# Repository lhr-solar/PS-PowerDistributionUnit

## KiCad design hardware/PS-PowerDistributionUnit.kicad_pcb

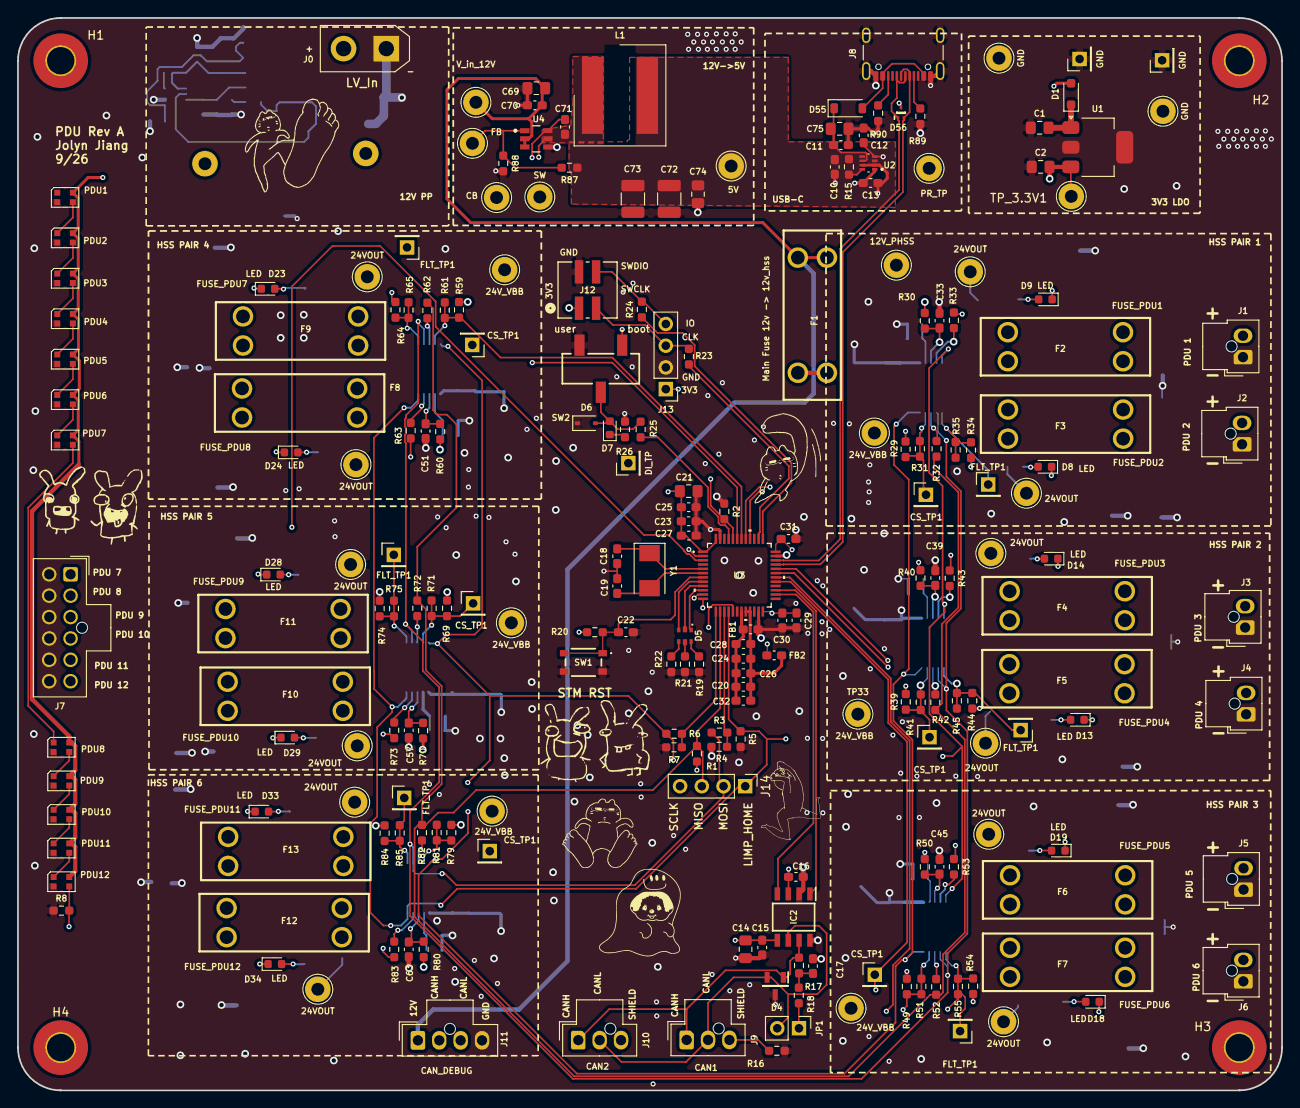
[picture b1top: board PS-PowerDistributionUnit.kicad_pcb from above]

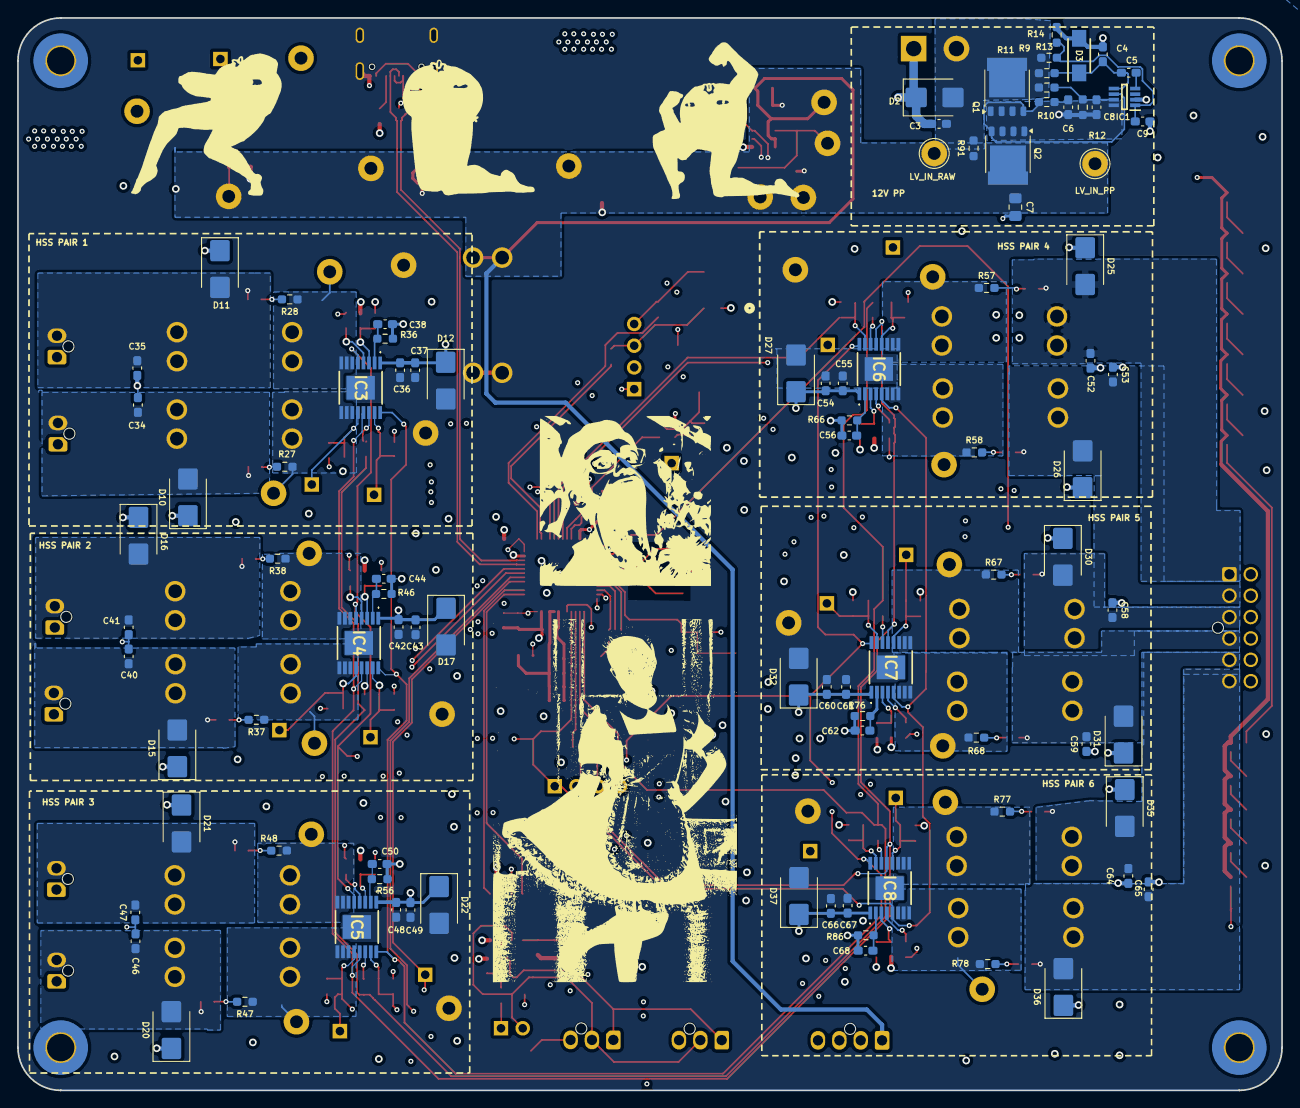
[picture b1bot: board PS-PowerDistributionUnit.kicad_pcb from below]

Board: 4 copper layers, 147.8 x 125.4 mm, 315 parts (93 on the bottom side), 142 nets.

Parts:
C1, C2, C7, C14: 10u; C_0805_2012Metric_Pad1.18x1.45mm_HandSolder
C3, C8, C9, C15, C16, C17: 0.1u; C_0603_1608Metric_Pad1.08x0.95mm_HandSolder
C4, C37, C43, C49, C55, C61, C67: 1u; C_0603_1608Metric_Pad1.08x0.95mm_HandSolder
C5: 220n; C_0603_1608Metric_Pad1.08x0.95mm_HandSolder
C6: 10n; C_0603_1608Metric_Pad1.08x0.95mm_HandSolder
C10, C11, C12, C13, C20, C22, C23, C24, C25, C27, C29, C30, C31: 0.1uF; C_0603_1608Metric_Pad1.08x0.95mm_HandSolder
C18, C19: 26p; C_0603_1608Metric_Pad1.08x0.95mm_HandSolder
C21, C75: 10uF; C_0805_2012Metric_Pad1.18x1.45mm_HandSolder
C26, C28: 1uF; C_0603_1608Metric_Pad1.08x0.95mm_HandSolder
C32: 100nF; C_0603_1608Metric_Pad1.08x0.95mm_HandSolder
C33, C39, C45, C51, C57, C63: 470n; C_0603_1608Metric_Pad1.08x0.95mm_HandSolder
C34, C35, C40, C41, C46, C47, C52, C53, C58, C59, C64, C65, C70, C71: 100n; C_0603_1608Metric_Pad1.08x0.95mm_HandSolder
C36, C42, C48, C54, C60, C66: 1n; C_0603_1608Metric_Pad1.08x0.95mm_HandSolder
C38, C44, C50, C56, C62, C68: 2.2n; C_0603_1608Metric_Pad1.08x0.95mm_HandSolder
C69: 4.7u; C_0805_2012Metric_Pad1.18x1.45mm_HandSolder
C72, C73: 22u; C_1210_3225Metric_Pad1.33x2.70mm_HandSolder
C74: 3.3u; C_0805_2012Metric_Pad1.18x1.45mm_HandSolder
D1: SBA130CH-AU_R1_000A1; D_SOD-323_HandSoldering
D2: SMBJ15CA; D_SMB
D3: SMAF4758A; SODFL5026X125N
D4: CDSOT23-T24CAN
D5: RGB_LED
D6: TVS; D_SOD-323
D7, D8, D9, D13, D14, D18, D19, D23, D24, D28, D29, D33, D34: LED; LED_0603_1608Metric
D10, D11, D12, D15, D16, D17, D20, D21, D22, D25, D26, D27, D30, D31, D32, D35, D36, D37: D_TVS; D_SMB
D38, D39, D40, D41, D42, D43, D44, D45, D46, D47, D48, D49: WS2812B-2020; LED_WS2812B-2020_PLCC4_2.0x2.0mm
D55: D_Schottky; D_SOD-123
D56: TPD2EUSB30DRTR
F1, F2, F3, F4, F5, F6, F7, F8, F9, F10, F11, F12, F13: 5A; Fuse-3557-2
FB1, FB2: FerriteBead; C_0603_1608Metric_Pad1.08x0.95mm_HandSolder
H1, H2, H3, H4: MountingHole_Pad; MountingHole_3.2mm_M3_Pad_TopBottom
IC1: LM74502DDFR
IC2: TCAN3413DR
IC3, IC4, IC5, IC6, IC7, IC8: TPS2HCS08AQPWPRQ1
J0: LV_IN; AMASS_XT30UPB-M_1x02_P5.0mm_Vertical
J1, J2, J3, J4, J5, J6: Conn_01x02; Molex_Nano-Fit_105309-xx02_1x02_P2.50mm_Vertical
J7: LV_0UT2; Molex_Nano-Fit_105310-xx12_2x06_P2.50mm_Vertical
J8: USB_C_Receptacle_USB2.0_16P; USB_C_Receptacle_GCT_USB4105-xx-A_16P_TopMnt_Horizontal
J9: CAN1; Molex_Nano-Fit_105309-xx03_1x03_P2.50mm_Vertical
J10: CAN2; Molex_Nano-Fit_105309-xx03_1x03_P2.50mm_Vertical
J11: CAN_DEBUG; Molex_Nano-Fit_105309-xx04_1x04_P2.50mm_Vertical
J12: SWD_Header; SWD_Conn
J13: SWD; PinHeader_1x04_P2.54mm_Vertical
J14: Conn_01x04; PinHeader_1x04_P2.54mm_Vertical
JP1: TRM; PinHeader_1x02_P2.54mm_Vertical
L1: 8.2u; 74439369082
Q1, Q2: PSMN012-100YS; LFPAK56
R1, R2, R4, R5, R7, R8, R9, R15, R20, R25, R29, R33, R35, R39, R43, R45, R49, R53, R55, R59, R63, R65, R69, R73, R75, R79, R83, R85: 10k; R_0603_1608Metric_Pad0.98x0.95mm_HandSolder
R3, R6, R23, R24, R31, R32, R41, R42, R51, R52, R61, R62, R71, R72, R81, R82: 22; R_0603_1608Metric_Pad0.98x0.95mm_HandSolder
R10: 33; R_0603_1608Metric_Pad0.98x0.95mm_HandSolder
R11, R13, R87: 100k; R_0603_1608Metric_Pad0.98x0.95mm_HandSolder
R12: 7.32k; R_0603_1608Metric_Pad0.98x0.95mm_HandSolder
R14: 15.8k; R_0603_1608Metric_Pad0.98x0.95mm_HandSolder
R16, R91: 0; R_0603_1608Metric_Pad0.98x0.95mm_HandSolder
R17, R18: 60; R_0603_1608Metric_Pad0.98x0.95mm_HandSolder
R19, R21, R22, R26, R36, R46, R56, R66, R76, R86: 1k; R_0603_1608Metric_Pad0.98x0.95mm_HandSolder
R27, R28, R34, R37, R38, R44, R47, R48, R54, R57, R58, R64, R67, R68, R74, R77, R78, R84: 4.7k; R_0603_1608Metric_Pad0.98x0.95mm_HandSolder
R30, R40, R50, R60, R70, R80: 10; R_0603_1608Metric_Pad0.98x0.95mm_HandSolder
R88: 19.1k; R_0603_1608Metric_Pad0.98x0.95mm_HandSolder
R89, R90: 5.1k; R_0603_1608Metric_Pad0.98x0.95mm_HandSolder
SW1: Reset; TL3365AF180QG
SW2: SW_SPDT; BootSW
TP4: DI_TP; PinHeader_1x01_P2.54mm_Vertical
TP6, TP7, TP8, TP9, TP10, TP11: FLT_TP1; PinHeader_1x01_P2.54mm_Vertical
TP12, TP13, TP14, TP15, TP16, TP17: CS_TP1; PinHeader_1x01_P2.54mm_Vertical
TP18: 12V_PHSS; TestPoint_THTPad_D3.0mm_Drill1.5mm
TP19, TP20: GND; TestPoint_THTPad_D3.0mm_Drill1.5mm
TP21, TP22: GND; PinHeader_1x01_P2.54mm_Vertical
TP23: LV_IN_RAW; TestPoint_THTPad_D3.0mm_Drill1.5mm
TP24: LV_IN_PP; TestPoint_THTPad_D3.0mm_Drill1.5mm
TP27: PR_TP; TestPoint_THTPad_D3.0mm_Drill1.5mm
TP28: 5V; TestPoint_THTPad_D3.0mm_Drill1.5mm
TP30, TP33, TP36, TP39, TP42, TP45: 24V_VBB; TestPoint_THTPad_D3.0mm_Drill1.5mm
TP31, TP32, TP34, TP35, TP37, TP38, TP40, TP41, TP43, TP44, TP46, TP47: 24VOUT; TestPoint_THTPad_D3.0mm_Drill1.5mm
TP48: V_in_12V; TestPoint_THTPad_D3.0mm_Drill1.5mm
TP49: CB; TestPoint_THTPad_D3.0mm_Drill1.5mm
TP50: FB; TestPoint_THTPad_D3.0mm_Drill1.5mm
TP51: SW; TestPoint_THTPad_D3.0mm_Drill1.5mm
TP_3.3V1: 3.3V; TestPoint_THTPad_D3.0mm_Drill1.5mm
U1: MCP1826S; SOT-223-3_TabPin2
U2: TPS2117DRLR
U3: STM32G473CETx; 48PinMCU
U4: LMR51635XDDCR; DDC0006A-MFG
Y1: Crystal; Crystal_SMD_Abracon_ABM3-2Pin_5.0x3.2mm

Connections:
+3V3: C2.2, C14.1, C15.1, C16.1, C21.1, C23.1, C25.1, C27.1, C29.1, C30.1, C31.1, FB2.1, IC2.3 (VCC), IC2.5 (SHDNV_IO), J12.1, J13.1, R1.2, R20.2, R29.1, R30.1, R34.1, R39.1, R40.1, R44.1, R49.1, R50.1, R54.1, R59.1, R60.1, R64.1, R69.1, R70.1, R74.1, R79.1, R80.1, R84.1, SW2.1 (A), TP_3.3V1.1 (1_1), U1.3 (VO), U3.1 (VBAT), U3.24 (VDD), U3.36 (VDD), U3.48 (VDD)
+5V: C13.1, D1.2 (A), D38.4 (VDD), D39.4 (VDD), D40.4 (VDD), D41.4 (VDD), D42.4 (VDD), D43.4 (VDD), D44.4 (VDD), D45.4 (VDD), D46.4 (VDD), D47.4 (VDD), D48.4 (VDD), D49.4 (VDD), U2.2 (VOUT), U2.7 (VOUT__1)
+12V: C7.1, C69.1, C70.1, F1.2, J11.1 (12V), Q2.5, R91.2, TP24.1 (1_1), TP48.1 (1_1), U4.2 (EN), U4.3 (VIN)
/48PinMCU/BOOT0: R25.1, U3.45 (PB8-BOOT0)
/48PinMCU/GNDA: C20.2, C24.2, C26.2, C28.2, C32.2, FB1.1, U3.19 (VSSA)
/48PinMCU/NRST: C22.1, R20.1, SW1.1, U3.7 (PG10-NRST)
/48PinMCU/PA0: D5.5, U3.8 (PA0-GPIO_BLUE)
/48PinMCU/PA1: D5.3, U3.9 (PA1_GPIO_RED)
/48PinMCU/PA2: D5.1, U3.10 (PA2-GPIO_GREEN)
/48PinMCU/PA5: R6.2, R7.2, U3.13 (PA5)
/48PinMCU/PA7: R3.2, R4.2, U3.15 (PA7)
/48PinMCU/PB1: D38.3 (DIN), R8.2, U3.17 (PB1)
/48PinMCU/PB12: IC2.4 (RXD), U3.26 (PB12)
/48PinMCU/PB13: IC2.1 (TXD), U3.27 (PB13)
/48PinMCU/SWCLK: R23.1, U3.38 (PA14)
/48PinMCU/SWDIO: R24.1, U3.37 (PA13)
/48PinMCU/VDDA: C20.1, C24.1, C26.1, C28.1, C32.1, FB2.2, U3.20 (VREF+), U3.21 (VDDA)
/+12V_HSS: C36.1, C37.1, C42.1, C43.1, C48.1, C49.1, C54.1, C55.1, C60.1, C61.1, C66.1, C67.1, D12.2 (A2), D17.2 (A2), D22.2 (A2), D27.2 (A2), D32.2 (A2), D37.2 (A2), F1.1, IC3.17 (VBB), IC4.17 (VBB), IC5.17 (VBB), IC6.17 (VBB), IC7.17 (VBB), IC8.17 (VBB), TP18.1 (1_1), TP30.1 (1_1), TP33.1 (1_1), TP36.1 (1_1), TP39.1 (1_1), TP42.1 (1_1), TP45.1 (1_1)
/CAN/CAN_H: D4.1 (CAN_H), IC2.7 (CANH), J9.1 (CAN_H), J10.1 (CAN_H), J11.2 (CAN_H), R17.1
/CAN/CAN_L: D4.2 (CAN_L), IC2.6 (CANL), J9.2 (CAN_L), J10.2 (CAN_L), J11.3 (CAN_L), JP1.2 (B)
/CAN/SHIELD: J9.3 (SHIELD), J10.3 (SHIELD), R16.1
/DI_MODE: R2.2, R33.1, R43.1, R53.1, R63.1, R73.1, R83.1, TP4.1 (1_1), U3.44 (PB7)
/LIMP_HOME: IC3.5 (LHI), IC4.5 (LHI), IC5.5 (LHI), IC6.5 (LHI), IC7.5 (LHI), IC8.5 (LHI), J14.1, R5.2, U3.16 (PB0)
/MISO: J14.3, R1.1, R32.1, R42.1, R52.1, R62.1, R72.1, R82.1, U3.14 (PA6)
/MOSI: IC3.13 (SDI), IC4.13 (SDI), IC5.13 (SDI), IC6.13 (SDI), IC7.13 (SDI), IC8.13 (SDI), J14.2, R3.1
/OUTPUT1: C35.2, D9.1 (K), D11.2 (A2), F2.2, J1.2
/OUTPUT2: C34.2, D8.1 (K), D10.2 (A2), F3.2, J2.2
/OUTPUT3: C41.2, D14.1 (K), D16.2 (A2), F4.2, J3.2
/OUTPUT4: C40.2, D13.1 (K), D15.2 (A2), F5.2, J4.2
/OUTPUT5: C47.2, D19.1 (K), D21.2 (A2), F6.2, J5.2
/OUTPUT6: C46.2, D18.1 (K), D20.2 (A2), F7.2, J6.2
/OUTPUT7: C52.2, D23.1 (K), D25.2 (A2), F9.2, J7.1
/OUTPUT8: C53.2, D24.1 (K), D26.2 (A2), F8.2, J7.2
/OUTPUT9: C58.2, D28.1 (K), D30.2 (A2), F11.2, J7.3
/OUTPUT10: C59.2, D29.1 (K), D31.2 (A2), F10.2, J7.4
/OUTPUT11: C64.2, D33.1 (K), D35.2 (A2), F13.2, J7.5
/OUTPUT12: C65.2, D34.1 (K), D36.2 (A2), F12.2, J7.6
/Pair1/FLT_WAKE: IC3.12 (~FLT_/_~WAKE_SIG), R34.2, R35.1, R35.2, TP6.1 (1_1), U3.41 (PB4)
/Pair1/SPI_CS: IC3.15 (NCS), R29.2, R31.1, R31.2, TP12.1 (1_1), U3.40 (PB3)
/Pair1/VDD: C33.1, IC3.3 (VDD), R30.2
/Pair1/VOUT1: F2.1, IC3.6 (VOUT1_1), IC3.7 (VOUT1_2), IC3.8 (VOUT1_3), R28.1, TP31.1 (1_1)
/Pair1/VOUT2: F3.1, IC3.9 (VOUT2_1), IC3.10 (VOUT2_2), IC3.11 (VOUT2_3), R27.1, TP32.1 (1_1)
/Pair2/FLT_WAKE: IC4.12 (~FLT_/_~WAKE_SIG), R44.2, R45.1, R45.2, TP7.1 (1_1), U3.32 (PA10)
/Pair2/SPI_CS: IC4.15 (NCS), R39.2, R41.1, R41.2, TP13.1 (1_1), U3.31 (PA9)
/Pair2/VDD: C39.1, IC4.3 (VDD), R40.2
/Pair2/VOUT1: F4.1, IC4.6 (VOUT1_1), IC4.7 (VOUT1_2), IC4.8 (VOUT1_3), R38.1, TP34.1 (1_1)
/Pair2/VOUT2: F5.1, IC4.9 (VOUT2_1), IC4.10 (VOUT2_2), IC4.11 (VOUT2_3), R37.1, TP35.1 (1_1)
/Pair3/FLT_WAKE: IC5.12 (~FLT_/_~WAKE_SIG), R54.2, R55.1, R55.2, TP8.1 (1_1), U3.30 (PA8)
/Pair3/SPI_CS: IC5.15 (NCS), R49.2, R51.1, R51.2, TP14.1 (1_1), U3.29 (PB15)
/Pair3/VDD: C45.1, IC5.3 (VDD), R50.2
/Pair3/VOUT1: F6.1, IC5.6 (VOUT1_1), IC5.7 (VOUT1_2), IC5.8 (VOUT1_3), R48.1, TP37.1 (1_1)
/Pair3/VOUT2: F7.1, IC5.9 (VOUT2_1), IC5.10 (VOUT2_2), IC5.11 (VOUT2_3), R47.1, TP38.1 (1_1)
/Pair4/FLT_WAKE: IC6.12 (~FLT_/_~WAKE_SIG), R64.2, R65.1, R65.2, TP9.1 (1_1), U3.43 (PB6)
/Pair4/SPI_CS: IC6.15 (NCS), R59.2, R61.1, R61.2, TP15.1 (1_1), U3.42 (PB5)
/Pair4/VDD: C51.1, IC6.3 (VDD), R60.2
/Pair4/VOUT1: F8.1, IC6.6 (VOUT1_1), IC6.7 (VOUT1_2), IC6.8 (VOUT1_3), R58.1, TP40.1 (1_1)
/Pair4/VOUT2: F9.1, IC6.9 (VOUT2_1), IC6.10 (VOUT2_2), IC6.11 (VOUT2_3), R57.1, TP41.1 (1_1)
/Pair5/FLT_WAKE: IC7.12 (~FLT_/_~WAKE_SIG), R74.2, R75.1, R75.2, TP10.1 (1_1), U3.3 (PC14-OSC32_IN)
/Pair5/SPI_CS: IC7.15 (NCS), R69.2, R71.1, R71.2, TP16.1 (1_1), U3.2 (PC13)
/Pair5/VDD: C57.1, IC7.3 (VDD), R70.2
/Pair5/VOUT1: F10.1, IC7.6 (VOUT1_1), IC7.7 (VOUT1_2), IC7.8 (VOUT1_3), R68.1, TP43.1 (1_1)
/Pair5/VOUT2: F11.1, IC7.9 (VOUT2_1), IC7.10 (VOUT2_2), IC7.11 (VOUT2_3), R67.1, TP44.1 (1_1)
/Pair6/FLT_WAKE: IC8.12 (~FLT_/_~WAKE_SIG), R84.2, R85.1, R85.2, TP11.1 (1_1), U3.11 (PA3)
/Pair6/SPI_CS: IC8.15 (NCS), R79.2, R81.1, R81.2, TP17.1 (1_1), U3.12 (PA4)
/Pair6/VDD: C63.1, IC8.3 (VDD), R80.2
/Pair6/VOUT1: F12.1, IC8.6 (VOUT1_1), IC8.7 (VOUT1_2), IC8.8 (VOUT1_3), R78.1, TP46.1 (1_1)
/Pair6/VOUT2: F13.1, IC8.9 (VOUT2_1), IC8.10 (VOUT2_2), IC8.11 (VOUT2_3), R77.1, TP47.1 (1_1)
/Power_usb/12VBuck/CB: C71.1, TP49.1 (1_1), U4.6 (CB)
/Power_usb/12VBuck/FB: R87.2, R88.1, TP50.1 (1_1), U4.1 (FB)
/Power_usb/12VBuck/SW: C71.2, L1.1, TP51.1 (1_1), U4.5 (SW)
/Power_usb/12V_INPUT: C3.1, D2.2 (A2), J0.2, Q1.5, R9.2, R11.1, R13.1, R91.1, TP23.1 (1_1)
/Power_usb/Buck_5V: C10.1, C72.1, C73.1, C74.1, L1.2, R15.1, R87.1, TP28.1 (1_1), U2.3 (VIN1), U2.5 (MODE)
/Power_usb/D+: D56.2 (D-), J8.A7 (D-), J8.B7 (D-), U3.33 (PA11)
/Power_usb/D-: D56.1 (D+), J8.A6 (D+), J8.B6 (D+), U3.34 (PA12)
/Power_usb/PowerProtection/EN/UVLO: C9.2, IC1.1 (EN/UVLO), R13.2, R14.2
/Power_usb/PowerProtection/OV: C8.2, IC1.7 (OV), R11.2, R12.1
/Power_usb/PowerProtection/gate: IC1.6 (GATE), Q1.4, Q2.4, R10.2
/Power_usb/PowerProtection/source: IC1.8 (SRC), Q1.1, Q1.2, Q1.3, Q2.1, Q2.2, Q2.3
/Power_usb/Power_Mux/PR1: C12.1, TP27.1 (1_1), U2.4 (PR1)
/Power_usb/Power_Mux/VIN_2: C11.1, C75.2, D55.1 (K), U2.6 (VIN2)
/Power_usb/USB-C Connector/CC1: J8.A5 (CC1), R89.2
/Power_usb/USB-C Connector/CC2: J8.B5 (CC2), R90.2
/Power_usb/USB-C Connector/VBUS_IN: D55.2 (A), J8.A4 (VBUS), J8.A9 (VBUS), J8.B4 (VBUS), J8.B9 (VBUS)
/SCLK: IC3.16 (SCLK), IC4.16 (SCLK), IC5.16 (SCLK), IC6.16 (SCLK), IC7.16 (SCLK), IC8.16 (SCLK), J14.4, R6.1
GND: C1.1, C2.1, C3.2, C4.1, C6.2, C7.2, C8.1, C9.1, C10.2, C11.2, C12.2, C13.2, C14.2, C15.2, C16.2, C17.1, C18.1, C19.2, C21.2, C22.2, C23.2, C25.2, C27.2, C29.2, C30.2, C31.2, C33.2, C34.1, C35.1, C36.2, C37.2, C38.2, C39.2, C40.1, C41.1, C42.2, C43.2, C44.2, C45.2, C46.1, C47.1, C48.2, C49.2, C50.2, C51.2, C52.1, C53.1, C54.2, C55.2, C56.2, C57.2, C58.1, C59.1, C60.2, C61.2, C62.2, C63.2, C64.1, C65.1, C66.2, C67.2, C68.2, C69.2, C70.2, C72.2, C73.2, C74.2, C75.1, D2.1 (A1), D3.2 (A), D4.3 (GND), D6.1 (A1), D10.1 (A1), D11.1 (A1), D12.1 (A1), D15.1 (A1), D16.1 (A1), D17.1 (A1), D20.1 (A1), D21.1 (A1), D22.1 (A1), D25.1 (A1), D26.1 (A1), D27.1 (A1), D30.1 (A1), D31.1 (A1), D32.1 (A1), D35.1 (A1), D36.1 (A1), D37.1 (A1), D38.2 (VSS), D39.2 (VSS), D40.2 (VSS), D41.2 (VSS), D42.2 (VSS), D43.2 (VSS), D44.2 (VSS), D45.2 (VSS), D46.2 (VSS), D47.2 (VSS), D48.2 (VSS), D49.2 (VSS), D56.3 (GND), FB1.2, IC1.2 (GND), IC2.2 (GND), IC2.8 (STB), IC3.1 (GND), IC4.1 (GND), IC5.1 (GND), IC6.1 (GND), IC7.1 (GND), IC8.1 (GND), J0.1, J1.1, J2.1, J3.1, J4.1, J5.1, J6.1, J7.7, J7.8, J7.9, J7.10, J7.11, J7.12, J8.A1 (GND), J8.A12 (GND), J8.B1 (GND), J8.B12 (GND), J8.S1 (SHIELD), J8.S2 (Shield), J8.S3 (Shield), J8.S4 (Shield), J11.4 (GND), J12.2, J13.2, R2.1, R4.1, R5.1, R7.1, R8.1, R12.2, R14.1, R16.2, R19.2, R21.2, R22.2, R26.2, R36.1, R46.1, R56.1, R66.1, R76.1, R86.1, R88.2, R89.1, R90.1, SW1.2, SW2.3 (C), TP19.1 (1_1), TP20.1 (1_1), TP21.1 (1_1), TP22.1 (1_1), U1.2 (GND), U2.1 (GND), U3.23 (VSS), U3.35 (VSS), U3.47 (VSS), U4.4 (GND)
unnamed: C6.1, R10.1
unnamed: C17.2, R17.2, R18.1
unnamed: C1.2, D1.1 (K), U1.1 (VI)
unnamed: C4.2, C5.1, D3.1 (K), IC1.5 (VS), R9.1
unnamed: D5.2, R19.1
unnamed: D5.4, R21.1
unnamed: D5.6, R22.1
unnamed: D6.2 (A2), D7.2 (A), R25.2, SW2.2 (B)
unnamed: D7.1 (K), R26.1
unnamed: D8.2 (A), R27.2
unnamed: D9.2 (A), R28.2
unnamed: D13.2 (A), R37.2
unnamed: D14.2 (A), R38.2
unnamed: D18.2 (A), R47.2
unnamed: D19.2 (A), R48.2
unnamed: D23.2 (A), R57.2
unnamed: D24.2 (A), R58.2
unnamed: D28.2 (A), R67.2
unnamed: D29.2 (A), R68.2
unnamed: D33.2 (A), R77.2
unnamed: D34.2 (A), R78.2
unnamed: D38.1 (DOUT), D39.3 (DIN)
unnamed: D39.1 (DOUT), D40.3 (DIN)
unnamed: D40.1 (DOUT), D41.3 (DIN)
unnamed: D41.1 (DOUT), D42.3 (DIN)
unnamed: D42.1 (DOUT), D44.3 (DIN)
unnamed: D43.3 (DIN), D45.1 (DOUT)
unnamed: D44.1 (DOUT), D46.3 (DIN)
unnamed: D45.3 (DIN), D47.1 (DOUT)
unnamed: D46.1 (DOUT), D48.3 (DIN)
unnamed: D47.3 (DIN), D49.1 (DOUT)
unnamed: D48.1 (DOUT), D49.3 (DIN)
unnamed: C5.2, IC1.4 (VCAP)
unnamed: IC3.4 (DI), R33.2
unnamed: IC3.14 (SDO), R32.2
unnamed: C38.1, IC3.2 (SNS), R36.2
unnamed: IC4.4 (DI), R43.2
unnamed: IC4.14 (SDO), R42.2
unnamed: C44.1, IC4.2 (SNS), R46.2
unnamed: IC5.4 (DI), R53.2
unnamed: IC5.14 (SDO), R52.2
unnamed: C50.1, IC5.2 (SNS), R56.2
unnamed: IC6.4 (DI), R63.2
unnamed: IC6.14 (SDO), R62.2
unnamed: C56.1, IC6.2 (SNS), R66.2
unnamed: IC7.4 (DI), R73.2
unnamed: IC7.14 (SDO), R72.2
unnamed: C62.1, IC7.2 (SNS), R76.2
unnamed: IC8.4 (DI), R83.2
unnamed: IC8.14 (SDO), R82.2
unnamed: C68.1, IC8.2 (SNS), R86.2
unnamed: J12.3, J13.3, R23.2
unnamed: J12.4, J13.4, R24.2
unnamed: JP1.1 (A), R18.2
unnamed: R15.2, U2.8 (ST)
unnamed: C18.2, U3.5 (PF0-OSC_IN), Y1.1
unnamed: C19.1, U3.6 (PF1-OSC_OUT), Y1.2

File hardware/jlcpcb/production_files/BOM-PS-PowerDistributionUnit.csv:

Comment,Designator,Footprint,LCSC,Quantity
0.1u,"C15,C16,C17,C3,C8,C9",C_0603_1608Metric_Pad1.08x0.95mm_HandSolder,C1591,6
0.1uF,"C10,C11,C12,C13,C20,C22,C23,C24,C25,C27,C29,C30,C31",C_0603_1608Metric_Pad1.08x0.95mm_HandSolder,C1591,13
10,"R30,R40,R50,R60,R70,R80",R_0603_1608Metric_Pad0.98x0.95mm_HandSolder,C313648,6
100k,"R11,R13,R87",R_0603_1608Metric_Pad0.98x0.95mm_HandSolder,C25803,3
100n,"C34,C35,C40,C41,C46,C47,C52,C53,C58,C59,C64,C65,C70,C71",C_0603_1608Metric_Pad1.08x0.95mm_HandSolder,C1591,14
100nF,C32,C_0603_1608Metric_Pad1.08x0.95mm_HandSolder,C1591,1
10k,"R1,R15,R2,R20,R25,R29,R33,R35,R39,R4,R43,R45,R49,R5,R53,R55,R59,R63,R65,R69,R7,R73,R75,R79,R8,R83,R85,R9",R_0603_1608Metric_Pad0.98x0.95mm_HandSolder,C25804,28
10n,C6,C_0603_1608Metric_Pad1.08x0.95mm_HandSolder,C57112,1
10u,"C1,C14,C2,C7",C_0805_2012Metric_Pad1.18x1.45mm_HandSolder,C440198,4
10uF,"C21,C75",C_0805_2012Metric_Pad1.18x1.45mm_HandSolder,C440198,2
15.8k,R14,R_0603_1608Metric_Pad0.98x0.95mm_HandSolder,C2090646,1
19.1k,R88,R_0603_1608Metric_Pad0.98x0.95mm_HandSolder,C844132,1
1k,"R19,R21,R22,R26,R36,R46,R56,R66,R76,R86",R_0603_1608Metric_Pad0.98x0.95mm_HandSolder,C21190,10
1n,"C36,C42,C48,C54,C60,C66",C_0603_1608Metric_Pad1.08x0.95mm_HandSolder,C100040,6
1u,"C37,C4,C43,C49,C55,C61,C67",C_0603_1608Metric_Pad1.08x0.95mm_HandSolder,C15849,7
1uF,"C26,C28",C_0603_1608Metric_Pad1.08x0.95mm_HandSolder,C15849,2
2.2n,"C38,C44,C50,C56,C62,C68",C_0603_1608Metric_Pad1.08x0.95mm_HandSolder,C5254613,6
22,"R23,R24,R3,R31,R32,R41,R42,R51,R52,R6,R61,R62,R71,R72,R81,R82",R_0603_1608Metric_Pad0.98x0.95mm_HandSolder,C107701,16
220n,C5,C_0603_1608Metric_Pad1.08x0.95mm_HandSolder,C344195,1
22u,"C72,C73",C_1210_3225Metric_Pad1.33x2.70mm_HandSolder,C5448976,2
26p,"C18,C19",C_0603_1608Metric_Pad1.08x0.95mm_HandSolder,C92670,2
3.3u,C74,C_0805_2012Metric_Pad1.18x1.45mm_HandSolder,C342775,1
33,R10,R_0603_1608Metric_Pad0.98x0.95mm_HandSolder,C844927,1
4.7k,"R27,R28,R34,R37,R38,R44,R47,R48,R54,R57,R58,R64,R67,R68,R74,R77,R78,R84",R_0603_1608Metric_Pad0.98x0.95mm_HandSolder,C23162,18
4.7u,C69,C_0805_2012Metric_Pad1.18x1.45mm_HandSolder,C105911,1
470n,"C33,C39,C45,C51,C57,C63",C_0603_1608Metric_Pad1.08x0.95mm_HandSolder,C106851,6
5.1k,"R89,R90",R_0603_1608Metric_Pad0.98x0.95mm_HandSolder,C23186,2
5A,"F1,F10,F11,F12,F13,F2,F3,F4,F5,F6,F7,F8,F9",Fuse-3557-2,C3205238,13
60,"R17,R18",R_0603_1608Metric_Pad0.98x0.95mm_HandSolder,C166918,2
7.32k,R12,R_0603_1608Metric_Pad0.98x0.95mm_HandSolder,C25804,1
8.2u,L1,74439369082,C1870586,1
CAN1,J9,Molex_Nano-Fit_105309-xx03_1x03_P2.50mm_Vertical,C17504794,1
CAN2,J10,Molex_Nano-Fit_105309-xx03_1x03_P2.50mm_Vertical,C17504794,1
CAN_DEBUG,J11,Molex_Nano-Fit_105309-xx04_1x04_P2.50mm_Vertical,C586230,1
CDSOT23-T24CAN,D4,CDSOT23-T24CAN,C2959841,1
CS_TP1,"TP12,TP13,TP14,TP15,TP16,TP17",PinHeader_1x01_P2.54mm_Vertical,C41426955,6
Conn_01x02,"J1,J2,J3,J4,J5,J6",Molex_Nano-Fit_105309-xx02_1x02_P2.50mm_Vertical,C2938824,6
Crystal,Y1,Crystal_SMD_Abracon_ABM3-2Pin_5.0x3.2mm,C144380,1
DI_TP,TP4,PinHeader_1x01_P2.54mm_Vertical,C41426955,1
D_Schottky,D55,D_SOD-123,C82544,1
D_TVS,"D10,D11,D12,D15,D16,D17,D20,D21,D22,D25,D26,D27,D30,D31,D32,D35,D36,D37",D_SMB,C428853,18
FLT_TP1,"TP10,TP11,TP6,TP7,TP8,TP9",PinHeader_1x01_P2.54mm_Vertical,C41426955,6
FerriteBead,"FB1,FB2",C_0603_1608Metric_Pad1.08x0.95mm_HandSolder,C354394,2
GND,"TP21,TP22",PinHeader_1x01_P2.54mm_Vertical,C41426955,2
LED,D7,LED_0603_1608Metric,C125103,1
LED,"D13,D14,D18,D19,D23,D24,D28,D29,D33,D34,D8,D9",LED_0603_1608Metric,C84263,12
LM74502DDFR,IC1,LM74502DDFR,C3236215,1
LMR51635XDDCR,U4,DDC0006A-MFG,C42432812,1
LV_0UT2,J7,Molex_Nano-Fit_105310-xx12_2x06_P2.50mm_Vertical,C485572,1
MCP1826S,U1,SOT-223-3_TabPin2,C126055,1
PSMN012-100YS,"Q1,Q2",LFPAK56,C20443035,2
RGB_LED,D5,RGB_LED,C264519,1
Reset,SW1,TL3365AF180QG,C2886926,1
SBA130CH-AU_R1_000A1,D1,D_SOD-323_HandSoldering,C191023,1
SMAF4758A,D3,SODFL5026X125N,C183490,1
SMBJ15CA,D2,D_SMB,C669039,1
STM32G473CETx,U3,48PinMCU,C730113,1
SWD,J13,PinHeader_1x04_P2.54mm_Vertical,C2691448,1
SWD_Header,J12,SWD_Conn,C17492485,1
TCAN3413DR,IC2,TCAN3413DR,C22433320,1
TPD2EUSB30DRTR,D56,TPD2EUSB30DRTR,C97502,1
TPS2117DRLR,U2,TPS2117DRLR,C22399676,1
TRM,JP1,PinHeader_1x02_P2.54mm_Vertical,C492401,1
TVS,D6,D_SOD-323,C725495,1
WS2812B-2020,"D38,D39,D40,D41,D42,D43,D44,D45,D46,D47,D48,D49",LED_WS2812B-2020_PLCC4_2.0x2.0mm,C965555,12
24VOUT,TP37,TestPoint_THTPad_D3.0mm_Drill1.5mm,,1
12V_PHSS,TP18,TestPoint_THTPad_D3.0mm_Drill1.5mm,,1
24V_VBB,TP36,TestPoint_THTPad_D3.0mm_Drill1.5mm,,1
24VOUT,TP35,TestPoint_THTPad_D3.0mm_Drill1.5mm,,1
24VOUT,TP46,TestPoint_THTPad_D3.0mm_Drill1.5mm,,1
GND,TP20,TestPoint_THTPad_D3.0mm_Drill1.5mm,,1
Conn_01x04,J14,PinHeader_1x04_P2.54mm_Vertical,,1
USB_C_Receptacle_USB2.0_16P,J8,USB_C_Receptacle_GCT_USB4105-xx-A_16P_TopMnt_Horizontal,,1
24V_VBB,TP39,TestPoint_THTPad_D3.0mm_Drill1.5mm,,1
24VOUT,TP34,TestPoint_THTPad_D3.0mm_Drill1.5mm,,1
24V_VBB,TP45,TestPoint_THTPad_D3.0mm_Drill1.5mm,,1
24VOUT,TP31,TestPoint_THTPad_D3.0mm_Drill1.5mm,,1
SW_SPDT,SW2,BootSW,,1
LV_IN,J0,AMASS_XT30UPB-M_1x02_P5.0mm_Vertical,,1
24VOUT,TP32,TestPoint_THTPad_D3.0mm_Drill1.5mm,,1
SW,TP51,TestPoint_THTPad_D3.0mm_Drill1.5mm,,1
24V_VBB,TP30,TestPoint_THTPad_D3.0mm_Drill1.5mm,,1
PR_TP,TP27,TestPoint_THTPad_D3.0mm_Drill1.5mm,,1
24VOUT,TP41,TestPoint_THTPad_D3.0mm_Drill1.5mm,,1
24VOUT,TP43,TestPoint_THTPad_D3.0mm_Drill1.5mm,,1
5V,TP28,TestPoint_THTPad_D3.0mm_Drill1.5mm,,1
24V_VBB,TP42,TestPoint_THTPad_D3.0mm_Drill1.5mm,,1
24VOUT,TP44,TestPoint_THTPad_D3.0mm_Drill1.5mm,,1
24VOUT,TP40,TestPoint_THTPad_D3.0mm_Drill1.5mm,,1
V_in_12V,TP48,TestPoint_THTPad_D3.0mm_Drill1.5mm,,1
24V_VBB,TP33,TestPoint_THTPad_D3.0mm_Drill1.5mm,,1
24VOUT,TP47,TestPoint_THTPad_D3.0mm_Drill1.5mm,,1
24VOUT,TP38,TestPoint_THTPad_D3.0mm_Drill1.5mm,,1
GND,TP19,TestPoint_THTPad_D3.0mm_Drill1.5mm,,1
FB,TP50,TestPoint_THTPad_D3.0mm_Drill1.5mm,,1
CB,TP49,TestPoint_THTPad_D3.0mm_Drill1.5mm,,1
TPS2HCS08AQPWPRQ1,IC8,TPS2HCS08AQPWPRQ1,,1
TPS2HCS08AQPWPRQ1,IC4,TPS2HCS08AQPWPRQ1,,1
LV_IN_PP,TP24,TestPoint_THTPad_D3.0mm_Drill1.5mm,,1
TPS2HCS08AQPWPRQ1,IC3,TPS2HCS08AQPWPRQ1,,1
TPS2HCS08AQPWPRQ1,IC6,TPS2HCS08AQPWPRQ1,,1
TPS2HCS08AQPWPRQ1,IC7,TPS2HCS08AQPWPRQ1,,1
TPS2HCS08AQPWPRQ1,IC5,TPS2HCS08AQPWPRQ1,,1

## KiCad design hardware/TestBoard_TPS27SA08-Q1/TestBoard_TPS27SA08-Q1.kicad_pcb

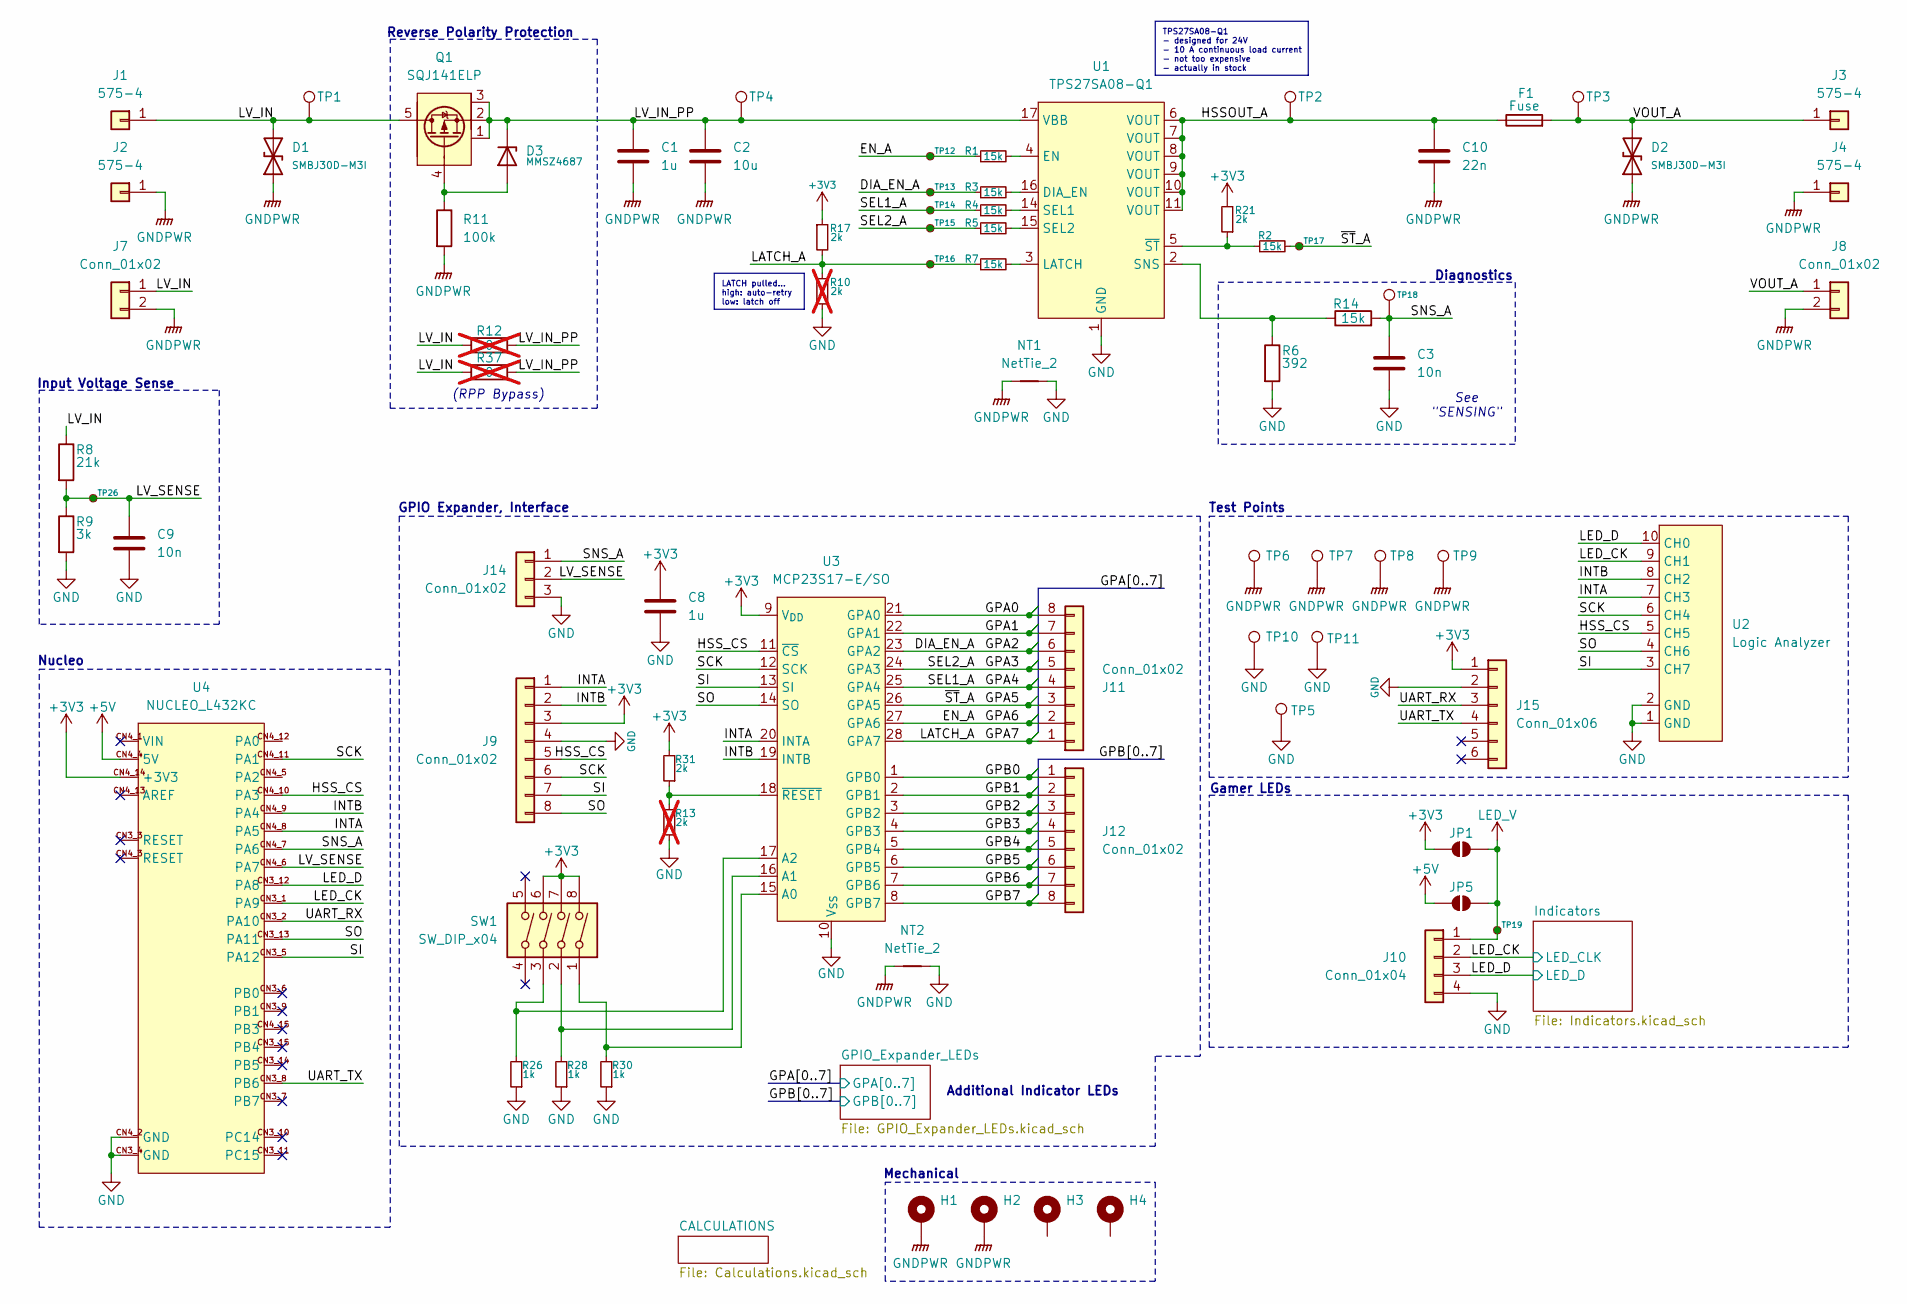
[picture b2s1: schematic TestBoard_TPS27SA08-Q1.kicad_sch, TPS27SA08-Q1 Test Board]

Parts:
C1, C8: 1u; C_0805_2012Metric
C2: 10u; C_0805_2012Metric
C3, C9: 10n; C_0805_2012Metric
C10: 22n; C_0805_2012Metric
D1, D2: SMBJ30D-M3I; D_SMB
D3: MMSZ4687; D_SOD-123
F1: Fuse; Fuseholder_Blade_Mini_Keystone_3568
H1, H2, H3, H4: MountingHole_Pad; MountingHole_3.2mm_M3_Pad
J1, J2, J3, J4: 575-4; 5754
J7, J8: Conn_01x02; TerminalBlock_MaiXu_MX126-5.0-02P_1x02_P5.00mm
J9, J11, J12: Conn_01x02; PinHeader_1x08_P2.54mm_Vertical
J10: Conn_01x04; PinHeader_1x04_P2.54mm_Vertical
J14: Conn_01x02; PinHeader_1x03_P2.54mm_Vertical
J15: Conn_01x06; PinSocket_1x06_P2.54mm_Vertical
JP1, JP5: SolderJumper_2_Open; SolderJumper-2_P1.3mm_Open_RoundedPad1.0x1.5mm
NT1, NT2: NetTie_2; NetTie-2_SMD_Pad0.5mm
Q1: SQJ141ELP; PowerPAK_SO-8L_Single
R1, R2, R3, R4, R5, R7, R14: 15k; R_0805_2012Metric
R6: 392; R_0805_2012Metric
R8: 21k; R_0805_2012Metric
R9: 3k; R_0805_2012Metric
R10, R13: 2k; R_0805_2012Metric; not fitted
R11: 100k; R_0805_2012Metric
R12, R37: 0; R_0805_2012Metric; not fitted
R17, R21, R31: 2k; R_0805_2012Metric
R26, R28, R30: 1k; R_0805_2012Metric
SW1: SW_DIP_x04; ADE04S04
TP1, TP2, TP3, TP4, TP5, TP6, TP7, TP8, TP9, TP10, TP11: TestPoint; PinHeader_1x01_P2.54mm_Vertical
TP12, TP13, TP14, TP15, TP16, TP17, TP19: TestPoint_Small; TestPoint_Pad_D1.0mm
TP18, TP26: TestPoint_Small; PinHeader_1x01_P2.54mm_Vertical
U1: TPS27SA08-Q1; HTSSOP-16-1EP_4.4x5mm_P0.65mm_EP3.4x5mm_Mask2.66x2.46mm_The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
U2: Logic Analyzer; CONN_SFH11-xxxC-D05-ST-XX_SUL
U3: MCP23S17-E/SO; SOIC-28W_7.5x17.9mm_P1.27mm
U4: NUCLEO_L432KC; MODULE_NUCLEO-L432KC

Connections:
+3V3: C8.1, J9.3, J15.1, JP1.1 (A), R17.1, R21.2, R31.2, SW1.6, SW1.7, SW1.8, U3.9 (V_{DD}), U4.CN4_14 (+3V3)
+5V: JP5.1 (A), U4.CN4_4 (5V)
/GPA0: J11.8, U3.21 (GPA0); also elsewhere on the board
/GPA1: J11.7, U3.22 (GPA1); also elsewhere on the board
/GPA2: J11.6, R3.1, TP13.1, U3.23 (GPA2); also elsewhere on the board
/GPA3: J11.5, R5.1, TP15.1, U3.24 (GPA3); also elsewhere on the board
/GPA4: J11.4, R4.1, TP14.1, U3.25 (GPA4); also elsewhere on the board
/GPA5: J11.3, R2.2, TP17.1, U3.26 (GPA5); also elsewhere on the board
/GPA6: J11.2, R1.1, TP12.1, U3.27 (GPA6); also elsewhere on the board
/GPA7: J11.1, R7.1, R10.1, R17.2, TP16.1, U3.28 (GPA7); also elsewhere on the board
/GPB0: J12.1, U3.1 (GPB0); also elsewhere on the board
/GPB1: J12.2, U3.2 (GPB1); also elsewhere on the board
/GPB2: J12.3, U3.3 (GPB2); also elsewhere on the board
/GPB3: J12.4, U3.4 (GPB3); also elsewhere on the board
/GPB4: J12.5, U3.5 (GPB4); also elsewhere on the board
/GPB5: J12.6, U3.6 (GPB5); also elsewhere on the board
/GPB6: J12.7, U3.7 (GPB6); also elsewhere on the board
/GPB7: J12.8, U3.8 (GPB7); also elsewhere on the board
/HSSOUT_A: C10.1, F1.1, TP2.1, U1.6 (VOUT), U1.7 (VOUT), U1.8 (VOUT), U1.9 (VOUT), U1.10 (VOUT), U1.11 (VOUT)
/HSS_CS: J9.5, U2.5 (CH5), U3.11 (~CS), U4.CN4_10 (PA3)
/INTA: J9.1, U2.7 (CH3), U3.20 (INTA), U4.CN4_8 (PA5)
/INTB: J9.2, U2.8 (CH2), U3.19 (INTB), U4.CN4_9 (PA4)
/LED_CK: J10.2, U2.9 (CH1), U4.CN3_1 (PA9); also elsewhere on the board
/LED_D: J10.3, U2.10 (CH0), U4.CN3_12 (PA8); also elsewhere on the board
/LV_IN: D1.2 (A2), J1.1, J7.1, Q1.5, R8.1, R12.1, R37.1, TP1.1
/LV_IN_PP: C1.1, C2.1, D3.1 (K), Q1.1, Q1.2, Q1.3, R12.2, R37.2, TP4.1, U1.17 (VBB)
/LV_SENSE: C9.1, J14.2, R8.2, R9.1, TP26.1, U4.CN4_6 (PA7)
/SCK: J9.6, U2.6 (CH4), U3.12 (SCK), U4.CN4_11 (PA1)
/SI: J9.7, U2.3 (CH7), U3.13 (SI), U4.CN3_5 (PA12)
/SNS_A: C3.1, J14.1, R14.2, TP18.1, U4.CN4_7 (PA6)
/SO: J9.8, U2.4 (CH6), U3.14 (SO), U4.CN3_13 (PA11)
/UART_RX: J15.3, U4.CN3_2 (PA10)
/UART_TX: J15.4, U4.CN3_8 (PB6)
/VOUT_A: D2.2 (A2), F1.2, J3.1, J8.1, TP3.1
GND: C3.2, C8.2, C9.2, J9.4, J10.4, J14.3, J15.2, NT1.2, NT2.2, R6.2, R9.2, R10.2, R13.1, R26.1, R28.1, R30.1, TP5.1, TP10.1, TP11.1, U1.1 (GND), U2.1 (GND), U2.2 (GND), U3.10 (V_{SS}), U4.CN3_4 (GND), U4.CN4_2 (GND); also elsewhere on the board
GNDPWR: C1.2, C2.2, C10.2, D1.1 (A1), D2.1 (A1), H1.1, H2.1, J2.1, J4.1, J7.2, J8.2, NT1.1, NT2.1, R11.2, TP6.1, TP7.1, TP8.1, TP9.1
LED_V: J10.1, JP1.2 (B), JP5.2 (B), TP19.1; also elsewhere on the board
unnamed: D3.2 (A), Q1.4, R11.1
unnamed: R3.2, U1.16 (DIA_EN)
unnamed: R1.2, U1.4 (EN)
unnamed: R7.2, U1.3 (LATCH)
unnamed: R4.2, U1.14 (SEL1)
unnamed: R5.2, U1.15 (SEL2)
unnamed: R6.1, R14.1, U1.2 (SNS)
unnamed: R2.1, R21.1, U1.5 (~ST)
unnamed: R30.2, SW1.1, U3.15 (A0)
unnamed: R28.2, SW1.2, U3.16 (A1)
unnamed: R26.2, SW1.3, U3.17 (A2)
unnamed: R13.2, R31.1, U3.18 (~RESET)

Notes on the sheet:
See "SENSING"
Reverse Polarity Protection
Mechanical
Input Voltage Sense
Diagnostics
Additional Indicator LEDs
(RPP Bypass)
Gamer LEDs
Test Points
GPIO Expander, Interface
Nucleo
LATCH pulled... high: auto-retry low: latch off
TPS27SA08-Q1 - designed for 24V - 10 A continuous load current - not too expensive - actually in stock

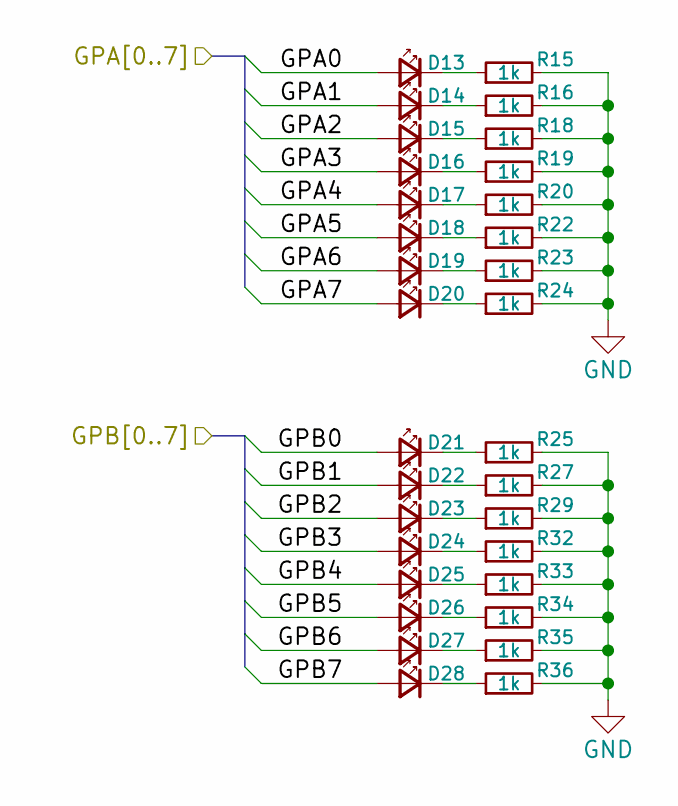
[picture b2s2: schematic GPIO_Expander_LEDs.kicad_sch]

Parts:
D13, D14, D15, D16, D17, D18, D19, D20, D21, D22, D23, D24, D25, D26, D27, D28: LED_Small; LED_0805_2012Metric
R15, R16, R18, R19, R20, R22, R23, R24, R25, R27, R29, R32, R33, R34, R35, R36: 1k; R_0805_2012Metric

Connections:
/GPA0: D13.2 (A); also elsewhere on the board
/GPA1: D14.2 (A); also elsewhere on the board
/GPA2: D15.2 (A); also elsewhere on the board
/GPA3: D16.2 (A); also elsewhere on the board
/GPA4: D17.2 (A); also elsewhere on the board
/GPA5: D18.2 (A); also elsewhere on the board
/GPA6: D19.2 (A); also elsewhere on the board
/GPA7: D20.2 (A); also elsewhere on the board
/GPB0: D21.2 (A); also elsewhere on the board
/GPB1: D22.2 (A); also elsewhere on the board
/GPB2: D23.2 (A); also elsewhere on the board
/GPB3: D24.2 (A); also elsewhere on the board
/GPB4: D25.2 (A); also elsewhere on the board
/GPB5: D26.2 (A); also elsewhere on the board
/GPB6: D27.2 (A); also elsewhere on the board
/GPB7: D28.2 (A); also elsewhere on the board
GND: R15.2, R16.2, R18.2, R19.2, R20.2, R22.2, R23.2, R24.2, R25.2, R27.2, R29.2, R32.2, R33.2, R34.2, R35.2, R36.2; also elsewhere on the board
unnamed: D13.1 (K), R15.1
unnamed: D14.1 (K), R16.1
unnamed: D15.1 (K), R18.1
unnamed: D16.1 (K), R19.1
unnamed: D17.1 (K), R20.1
unnamed: D18.1 (K), R22.1
unnamed: D19.1 (K), R23.1
unnamed: D20.1 (K), R24.1
unnamed: D21.1 (K), R25.1
unnamed: D22.1 (K), R27.1
unnamed: D23.1 (K), R29.1
unnamed: D24.1 (K), R32.1
unnamed: D25.1 (K), R33.1
unnamed: D26.1 (K), R34.1
unnamed: D27.1 (K), R35.1
unnamed: D28.1 (K), R36.1
